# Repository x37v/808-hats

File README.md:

# 808 hihat clone

Based on
[schematic](http://www.ericarcher.net/wp-content/uploads/2014/07/tr-808-hihat-diy-project-revised-dec-2009.pdf)
drawn by [Eric Archer](http://www.ericarcher.net/), which is in turn cloned from the TR-808 Hi Hat.

Drawn in [KiCad 5](http://kicad.org/).

## Mods

* MOTM Power connector
* Trigger conditioning
* Ext audio in
* Noise out
* OH/CH Filtering

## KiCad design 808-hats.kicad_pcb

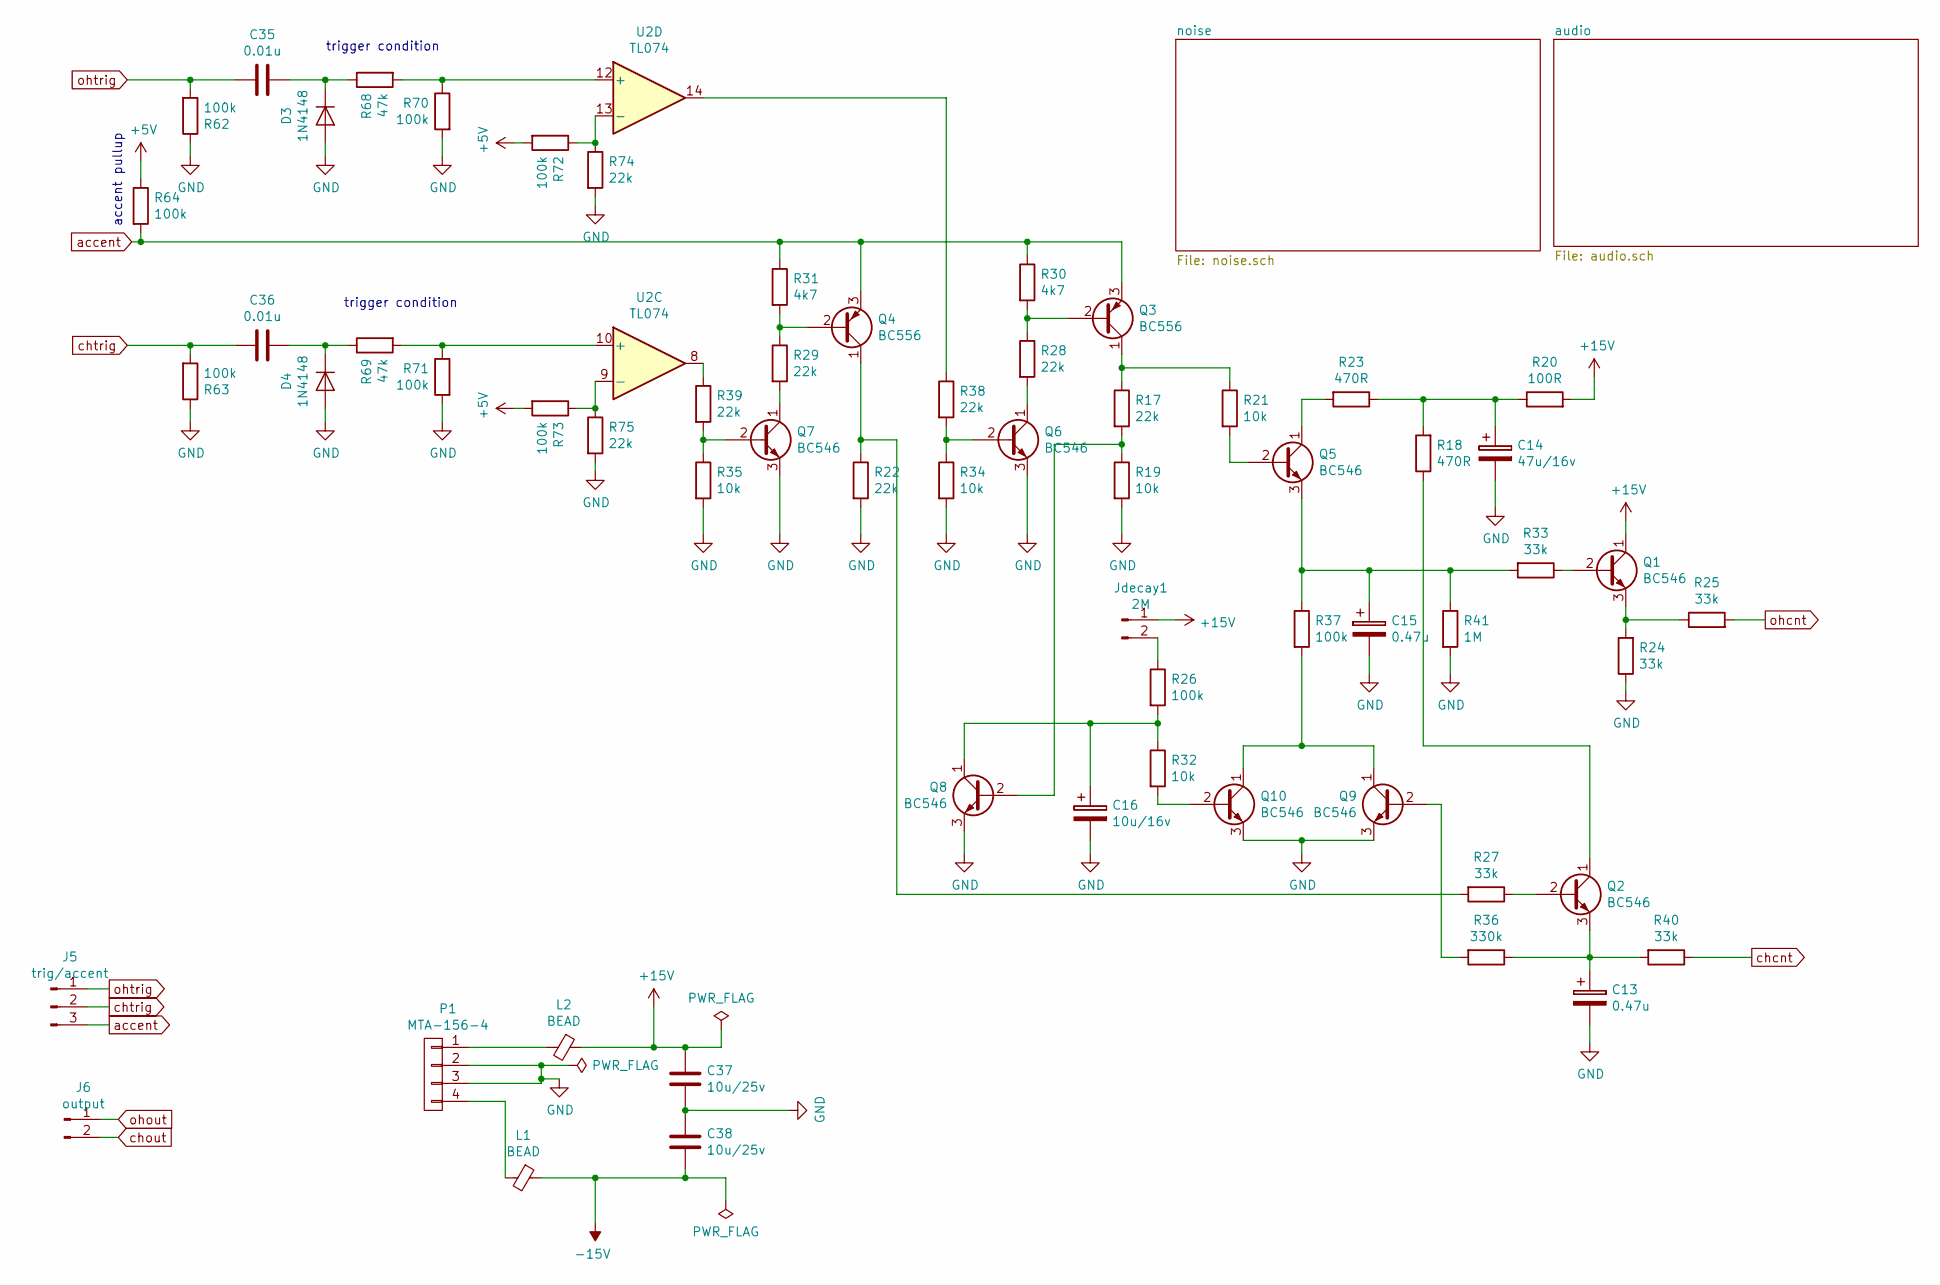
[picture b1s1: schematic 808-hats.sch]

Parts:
C13, C15: 0.47u; CP_Radial_D7.5mm_P2.50mm
C14: 47u/16v; CP_Radial_D7.5mm_P2.50mm
C16: 10u/16v; CP_Radial_D7.5mm_P2.50mm
C35, C36: 0.01u; C_Rect_L7.2mm_W3.0mm_P5.00mm_FKS2_FKP2_MKS2_MKP2
C37, C38: 10u/25v; C_0805_2012Metric_Pad1.33x1.40mm_HandSolder
D3, D4: 1N4148; D_DO-35_SOD27_P7.62mm_Horizontal
J5: trig/accent; PinHeader_1x03_P2.54mm_Vertical
J6: output; PinHeader_1x02_P2.54mm_Vertical
Jdecay1: 2M; PinHeader_1x02_P2.54mm_Vertical
L1, L2: BEAD; R_Axial_DIN0207_L6.3mm_D2.5mm_P10.16mm_Horizontal
P1: MTA-156-4
Q1, Q2, Q5, Q6, Q7, Q8, Q9, Q10: BC546; TO-92L_Inline
Q3, Q4: BC556; TO-92L_Inline
R17, R22, R28, R29, R38, R39, R74, R75: 22k; R_Axial_DIN0204_L3.6mm_D1.6mm_P7.62mm_Horizontal
R18, R23: 470R; R_Axial_DIN0204_L3.6mm_D1.6mm_P7.62mm_Horizontal
R19, R21, R32, R34, R35: 10k; R_Axial_DIN0204_L3.6mm_D1.6mm_P7.62mm_Horizontal
R20: 100R; R_Axial_DIN0204_L3.6mm_D1.6mm_P7.62mm_Horizontal
R24, R25, R27, R33, R40: 33k; R_Axial_DIN0204_L3.6mm_D1.6mm_P7.62mm_Horizontal
R26, R37, R62, R63, R64, R70, R71, R72, R73: 100k; R_Axial_DIN0204_L3.6mm_D1.6mm_P7.62mm_Horizontal
R30, R31: 4k7; R_Axial_DIN0204_L3.6mm_D1.6mm_P7.62mm_Horizontal
R36: 330k; R_Axial_DIN0204_L3.6mm_D1.6mm_P7.62mm_Horizontal
R41: 1M; R_Axial_DIN0204_L3.6mm_D1.6mm_P7.62mm_Horizontal
R68, R69: 47k; R_Axial_DIN0204_L3.6mm_D1.6mm_P7.62mm_Horizontal
U2: TL074; DIP-14_W7.62mm_LongPads

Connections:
+5V: R64.1, R72.2, R73.2; also elsewhere on the board
+15V: C37.1, Jdecay1.1, L2.1, Q1.1 (C), R20.2; also elsewhere on the board
-15V: C38.2, L1.1; also elsewhere on the board
GND: C13.2, C14.2, C15.2, C16.2, C37.2, C38.1, D3.2 (A), D4.2 (A), P1.2, P1.3, Q6.3 (E), Q7.3 (E), Q8.3 (E), Q9.3 (E), Q10.3 (E), R19.2, R22.2, R24.1, R34.2, R35.2, R41.2, R62.1, R63.1, R70.2, R71.2, R74.2, R75.2; also elsewhere on the board
unnamed: C13.1, Q2.3 (E), R36.1, R40.2
unnamed: C14.1, R18.2, R20.1, R23.1
unnamed: C15.1, Q5.3 (E), R33.2, R37.1, R41.1
unnamed: C16.1, Q8.1 (C), R26.2, R32.1
unnamed: C35.1, D3.1 (K), R68.1
unnamed: C36.1, D4.1 (K), R69.1
unnamed: Jdecay1.2, R26.1
unnamed: L1.2, P1.4
unnamed: L2.2, P1.1
unnamed: Q1.2 (B), R33.1
unnamed: Q1.3 (E), R24.2, R25.1
unnamed: Q2.1 (C), R18.1
unnamed: Q2.2 (B), R27.1
unnamed: Q3.1 (C), R17.1, R21.1
unnamed: Q3.2 (B), R28.1, R30.2
unnamed: Q4.1 (C), R22.1, R27.2
unnamed: Q4.2 (B), R29.1, R31.2
unnamed: Q5.1 (C), R23.2
unnamed: Q5.2 (B), R21.2
unnamed: Q6.1 (C), R28.2
unnamed: Q6.2 (B), R34.1, R38.2
unnamed: Q7.1 (C), R29.2
unnamed: Q7.2 (B), R35.1, R39.2
unnamed: Q8.2 (B), R17.2, R19.1
unnamed: Q9.2 (B), R36.2
unnamed: Q9.1 (C), Q10.1 (C), R37.2
unnamed: Q10.2 (B), R32.2
unnamed: R38.1, U2.14
unnamed: R39.1, U2.8
unnamed: R68.2, R70.1, U2.12 (+)
unnamed: R69.2, R71.1, U2.10 (+)
unnamed: R72.1, R74.1, U2.13 (-)
unnamed: R73.1, R75.1, U2.9 (-)
accent: J5.3, Q3.3 (E), Q4.3 (E), R30.1, R31.1, R64.2
chcnt: R40.1; also elsewhere on the board
chout: J6.2; also elsewhere on the board
chtrig: C36.2, J5.2, R63.2
ohcnt: R25.2; also elsewhere on the board
ohout: J6.1; also elsewhere on the board
ohtrig: C35.2, J5.1, R62.2

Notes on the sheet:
trigger condition
accent pullup

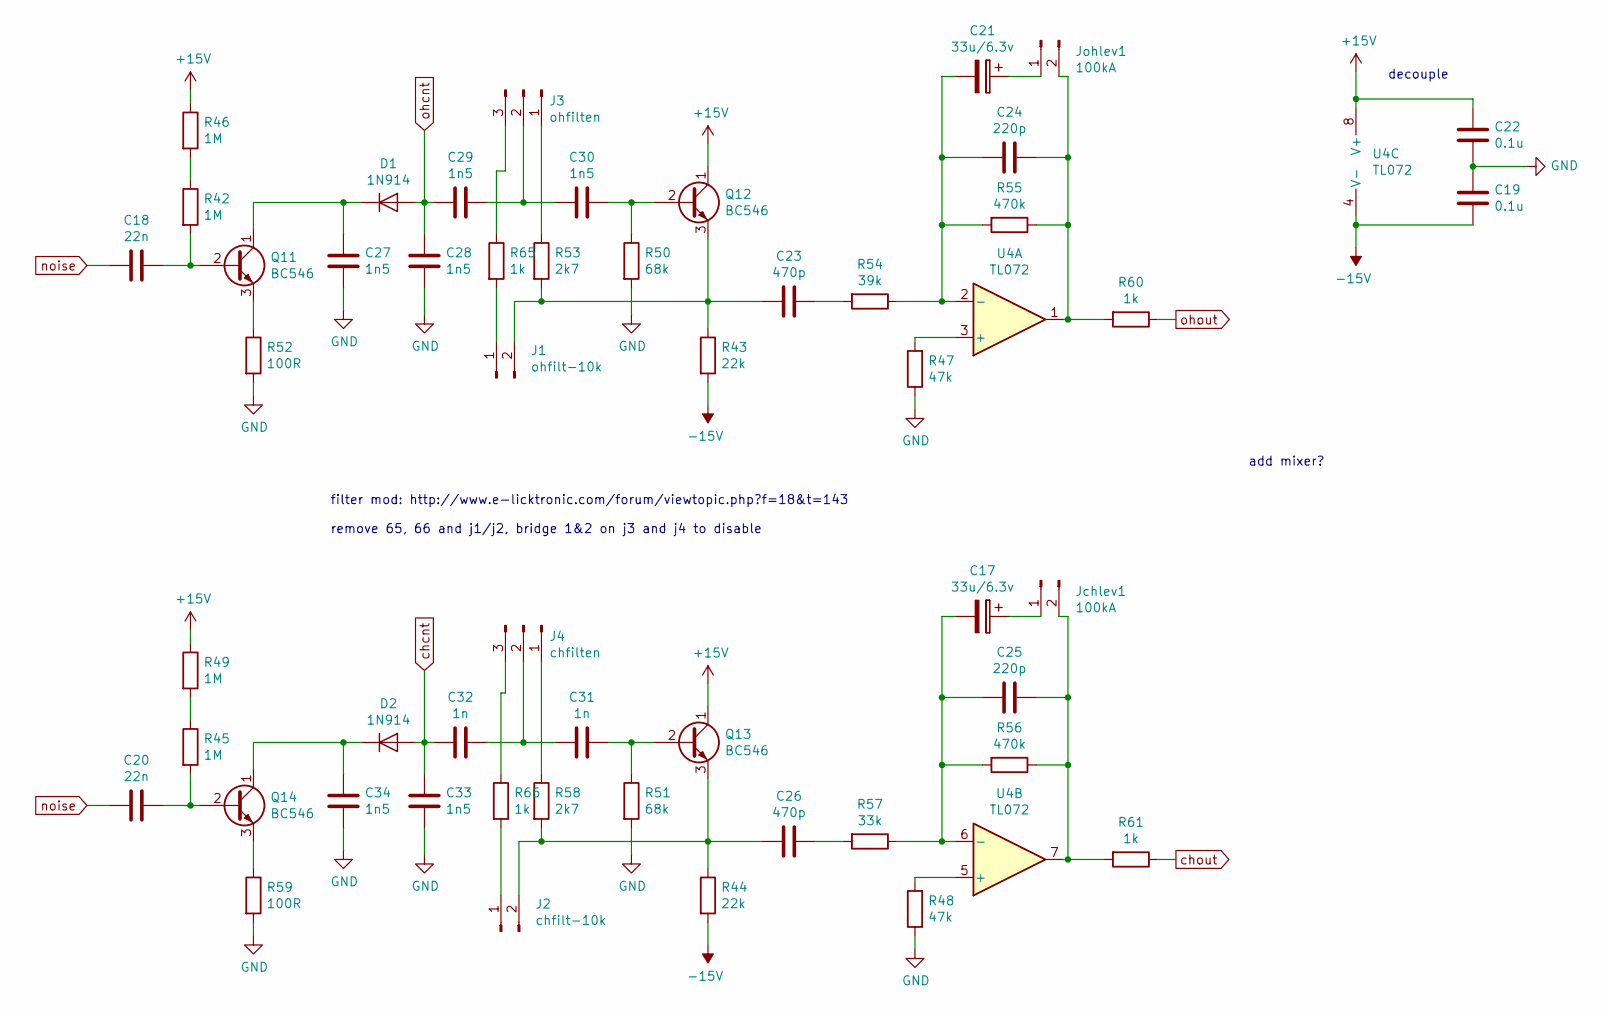
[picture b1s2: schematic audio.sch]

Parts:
C17, C21: 33u/6.3v; CP_Radial_D7.5mm_P2.50mm
C18, C20: 22n; C_Disc_D4.3mm_W1.9mm_P5.00mm
C19, C22: 0.1u; C_Disc_D3.4mm_W2.1mm_P2.50mm
C23, C26: 470p; C_Disc_D4.3mm_W1.9mm_P5.00mm
C24, C25: 220p; C_Disc_D4.3mm_W1.9mm_P5.00mm
C27, C28, C29, C30, C33, C34: 1n5; C_Disc_D3.4mm_W2.1mm_P2.50mm
C31, C32: 1n; C_Disc_D3.4mm_W2.1mm_P2.50mm
D1, D2: 1N914; D_DO-35_SOD27_P7.62mm_Horizontal
J1: ohfilt-10k; PinHeader_1x02_P2.54mm_Vertical
J2: chfilt-10k; PinHeader_1x02_P2.54mm_Vertical
J3: ohfilten; PinHeader_1x03_P2.54mm_Vertical
J4: chfilten; PinHeader_1x03_P2.54mm_Vertical
Jchlev1: 100kA; PinHeader_1x02_P2.54mm_Vertical
Johlev1: 100kA; PinHeader_1x02_P2.54mm_Vertical
Q11, Q12, Q13, Q14: BC546; TO-92L_Inline
R42, R45, R46, R49: 1M; R_Axial_DIN0204_L3.6mm_D1.6mm_P7.62mm_Horizontal
R43, R44: 22k; R_Axial_DIN0204_L3.6mm_D1.6mm_P7.62mm_Horizontal
R47, R48: 47k; R_Axial_DIN0204_L3.6mm_D1.6mm_P7.62mm_Horizontal
R50, R51: 68k; R_Axial_DIN0204_L3.6mm_D1.6mm_P7.62mm_Horizontal
R52, R59: 100R; R_Axial_DIN0204_L3.6mm_D1.6mm_P7.62mm_Horizontal
R53, R58: 2k7; R_Axial_DIN0204_L3.6mm_D1.6mm_P7.62mm_Horizontal
R54: 39k; R_Axial_DIN0204_L3.6mm_D1.6mm_P7.62mm_Horizontal
R55, R56: 470k; R_Axial_DIN0204_L3.6mm_D1.6mm_P7.62mm_Horizontal
R57: 33k; R_Axial_DIN0204_L3.6mm_D1.6mm_P7.62mm_Horizontal
R60, R61, R65, R66: 1k; R_Axial_DIN0204_L3.6mm_D1.6mm_P7.62mm_Horizontal
U4: TL072; DIP-8_W7.62mm_LongPads

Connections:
+15V: C22.1, Q12.1 (C), Q13.1 (C), R46.1, R49.1, U4.8 (V+); also elsewhere on the board
-15V: C19.2, R43.2, R44.2, U4.4 (V-); also elsewhere on the board
GND: C19.1, C22.2, C27.1, C28.1, C33.1, C34.1, R47.1, R48.1, R50.2, R51.2, R52.2, R59.2; also elsewhere on the board
unnamed: C17.1, Jchlev1.1
unnamed: C17.2, C25.2, R56.2, R57.1, U4.6 (-)
unnamed: C18.1, Q11.2 (B), R42.2
unnamed: C20.1, Q14.2 (B), R45.2
unnamed: C21.1, Johlev1.1
unnamed: C21.2, C24.2, R54.1, R55.2, U4.2 (-)
unnamed: C23.1, J1.2, Q12.3 (E), R43.1, R53.2
unnamed: C23.2, R54.2
unnamed: C24.1, Johlev1.2, R55.1, R60.2, U4.1
unnamed: C25.1, Jchlev1.2, R56.1, R61.2, U4.7
unnamed: C26.1, J2.2, Q13.3 (E), R44.1, R58.2
unnamed: C26.2, R57.2
unnamed: C27.2, D1.1 (K), Q11.1 (C)
unnamed: C29.2, C30.1, J3.2
unnamed: C30.2, Q12.2 (B), R50.1
unnamed: C31.1, C32.2, J4.2
unnamed: C31.2, Q13.2 (B), R51.1
unnamed: C34.2, D2.1 (K), Q14.1 (C)
unnamed: J1.1, R65.2
unnamed: J2.1, R66.2
unnamed: J3.1, R53.1
unnamed: J3.3, R65.1
unnamed: J4.1, R58.1
unnamed: J4.3, R66.1
unnamed: Q11.3 (E), R52.1
unnamed: Q14.3 (E), R59.1
unnamed: R42.1, R46.2
unnamed: R45.1, R49.2
unnamed: R47.2, U4.3 (+)
unnamed: R48.2, U4.5 (+)
chcnt: C32.1, C33.2, D2.2 (A); also elsewhere on the board
chout: R61.1; also elsewhere on the board
noise: C18.2, C20.2; also elsewhere on the board
ohcnt: C28.2, C29.1, D1.2 (A); also elsewhere on the board
ohout: R60.1; also elsewhere on the board

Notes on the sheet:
add mixer?
decouple
filter mod: http://www.e-licktronic.com/forum/viewtopic.php?f=18&t=143 remove 65, 66 and j1/j2, bridge 1&2 on j3 and j4 to disable

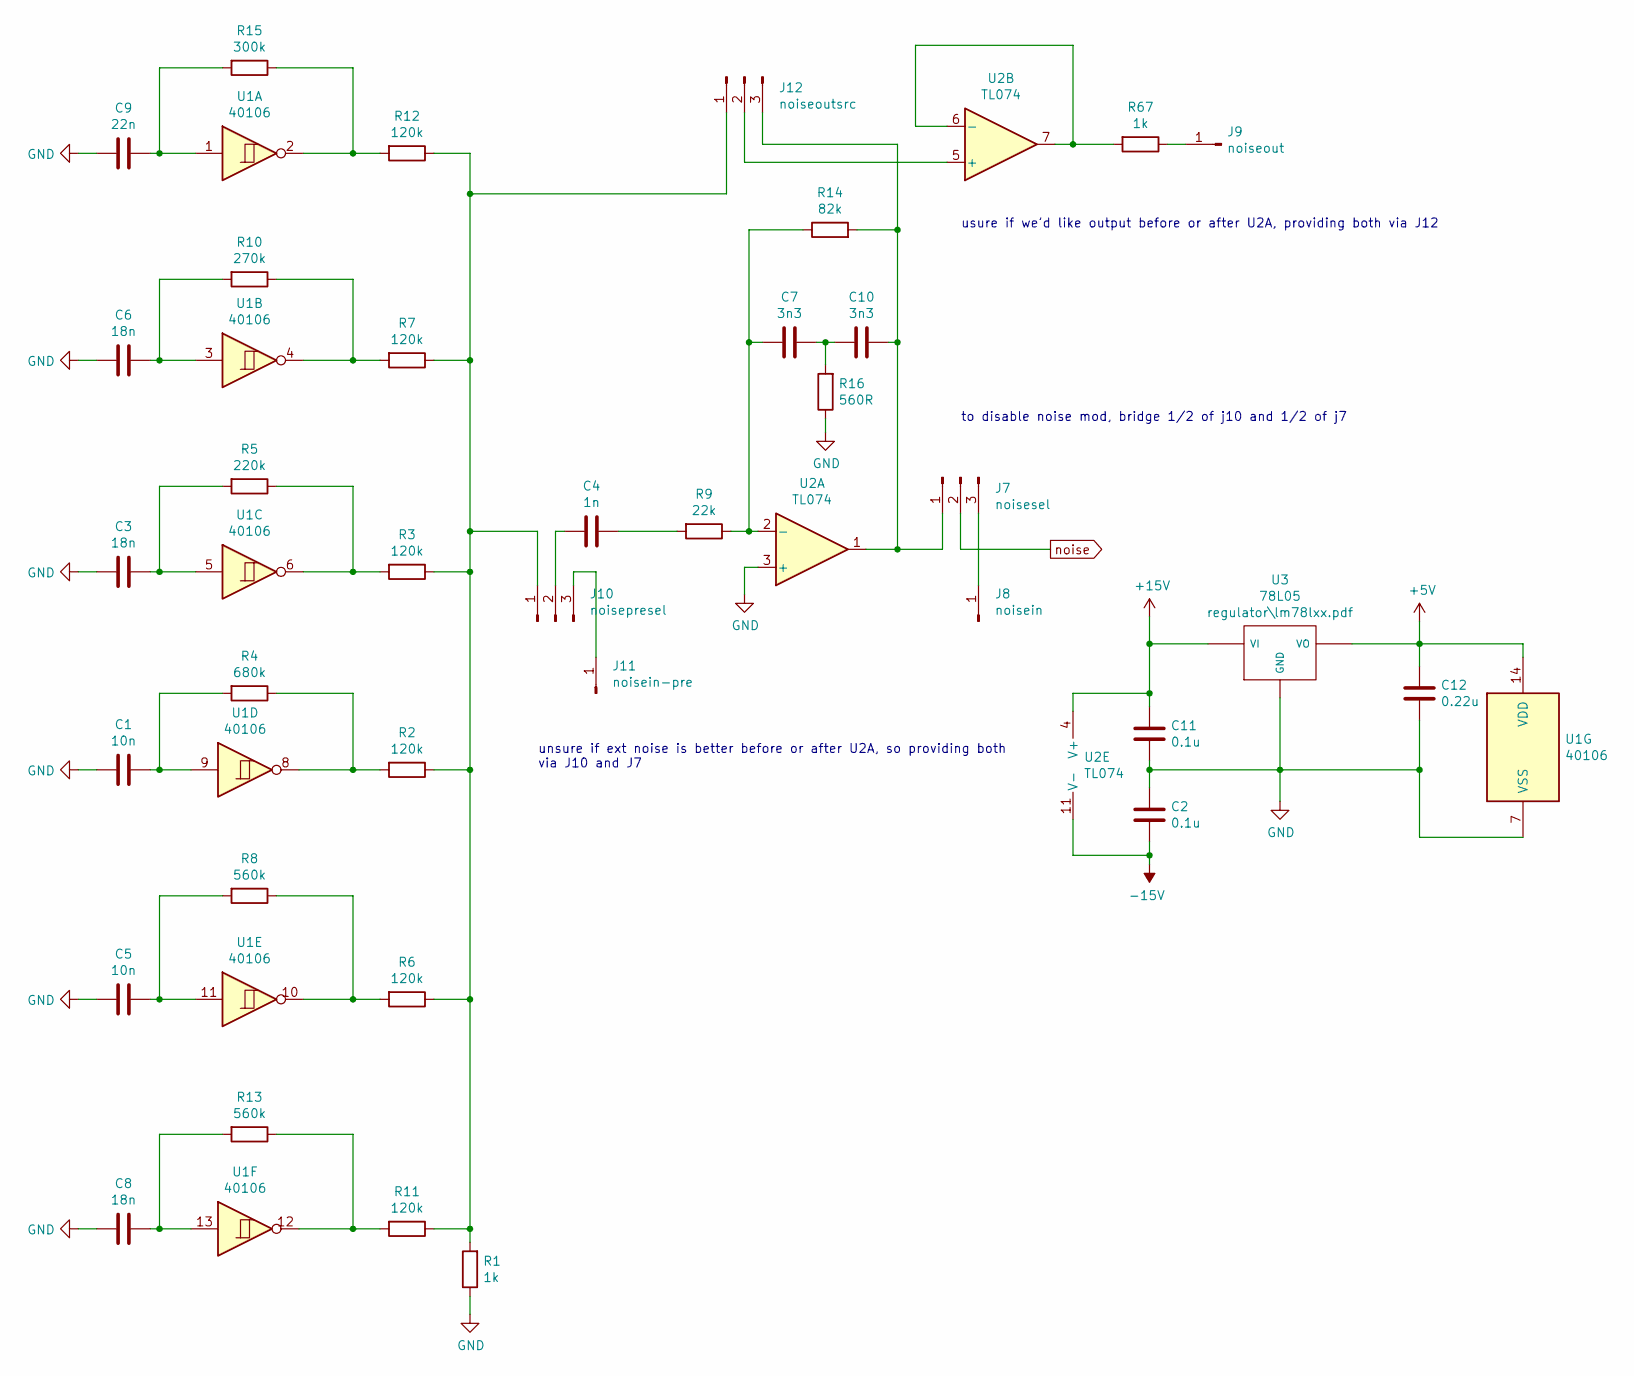
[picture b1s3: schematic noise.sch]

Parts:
C1, C5: 10n; C_Disc_D3.4mm_W2.1mm_P2.50mm
C2, C11: 0.1u; C_Disc_D3.4mm_W2.1mm_P2.50mm
C3, C6, C8: 18n; C_Disc_D3.4mm_W2.1mm_P2.50mm
C4: 1n; C_Disc_D3.4mm_W2.1mm_P2.50mm
C7, C10: 3n3; C_Disc_D3.4mm_W2.1mm_P2.50mm
C9: 22n; C_Disc_D4.3mm_W1.9mm_P5.00mm
C12: 0.22u; C_Disc_D3.4mm_W2.1mm_P2.50mm
J7: noisesel; PinHeader_1x03_P2.54mm_Vertical
J8: noisein; PinHeader_1x01_P2.54mm_Vertical
J9: noiseout; PinHeader_1x01_P2.54mm_Vertical
J10: noisepresel; PinHeader_1x03_P2.54mm_Vertical
J11: noisein-pre; PinHeader_1x01_P2.54mm_Vertical
J12: noiseoutsrc; PinHeader_1x03_P2.54mm_Vertical
R1, R67: 1k; R_Axial_DIN0204_L3.6mm_D1.6mm_P7.62mm_Horizontal
R2, R3, R6, R7, R11, R12: 120k; R_Axial_DIN0204_L3.6mm_D1.6mm_P7.62mm_Horizontal
R4: 680k; R_Axial_DIN0204_L3.6mm_D1.6mm_P7.62mm_Horizontal
R5: 220k; R_Axial_DIN0204_L3.6mm_D1.6mm_P7.62mm_Horizontal
R8, R13: 560k; R_Axial_DIN0204_L3.6mm_D1.6mm_P7.62mm_Horizontal
R9: 22k; R_Axial_DIN0204_L3.6mm_D1.6mm_P7.62mm_Horizontal
R10: 270k; R_Axial_DIN0204_L3.6mm_D1.6mm_P7.62mm_Horizontal
R14: 82k; R_Axial_DIN0204_L3.6mm_D1.6mm_P7.62mm_Horizontal
R15: 300k; R_Axial_DIN0204_L3.6mm_D1.6mm_P7.62mm_Horizontal
R16: 560R; R_Axial_DIN0204_L3.6mm_D1.6mm_P7.62mm_Horizontal
U1: 40106; DIP-14_W7.62mm_LongPads
U2: TL074; DIP-14_W7.62mm_LongPads
U3: 78L05; TO-220-3_Vertical

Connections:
+5V: C12.1, U1.14 (VDD), U3.3 (VO); also elsewhere on the board
+15V: C11.1, U2.4 (V+), U3.1 (VI); also elsewhere on the board
-15V: C2.2, U2.11 (V-); also elsewhere on the board
GND: C1.2, C2.1, C3.2, C5.2, C6.2, C8.2, C9.2, C11.2, C12.2, R1.1, R16.1, U1.7 (VSS), U2.3 (+), U3.2 (GND); also elsewhere on the board
unnamed: C1.1, R4.2, U1.9
unnamed: C3.1, R5.2, U1.5
unnamed: C4.1, R9.2
unnamed: C4.2, J10.2
unnamed: C5.1, R8.2, U1.11
unnamed: C6.1, R10.2, U1.3
unnamed: C7.2, R9.1, R14.1, U2.2 (-)
unnamed: C8.1, R13.2, U1.13
unnamed: C9.1, R15.2, U1.1
unnamed: C10.1, J7.1, J12.3, R14.2, U2.1
unnamed: C7.1, C10.2, R16.2
unnamed: J7.3, J8.1
unnamed: J9.1, R67.1
unnamed: J10.1, J12.1, R1.2, R2.1, R3.1, R6.1, R7.1, R11.1, R12.1
unnamed: J10.3, J11.1
unnamed: J12.2, U2.5 (+)
unnamed: R2.2, R4.1, U1.8
unnamed: R3.2, R5.1, U1.6
unnamed: R6.2, R8.1, U1.10
unnamed: R7.2, R10.1, U1.4
unnamed: R11.2, R13.1, U1.12
unnamed: R12.2, R15.1, U1.2
unnamed: R67.2, U2.6 (-), U2.7
noise: J7.2; also elsewhere on the board

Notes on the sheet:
unsure if ext noise is better before or after U2A, so providing both via J10 and J7
usure if we'd like output before or after U2A, providing both via J12
to disable noise mod, bridge 1/2 of j10 and 1/2 of j7

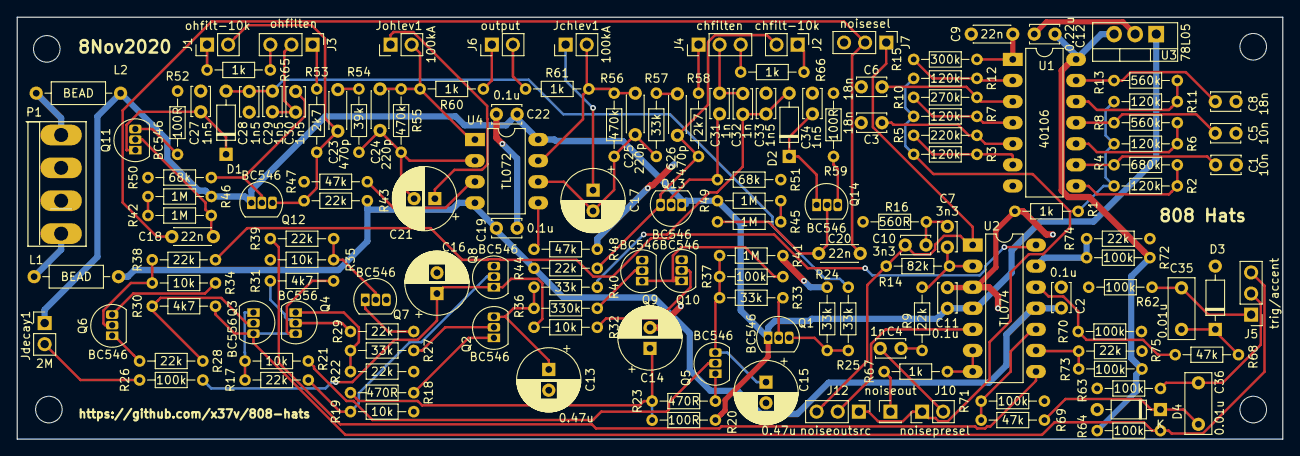
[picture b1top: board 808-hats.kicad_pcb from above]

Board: 2 copper layers, 152.4 x 50.8 mm, 149 parts (0 on the bottom side), 96 nets.

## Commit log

2019-04-13 initial commit
    need to add trigger conditioning
2019-04-13 added trigger conditioning and accent pullup
2019-04-13 added power
2019-04-14 fixup noise generator connections
2019-04-14 added filter mod
2019-04-14 noise in/out with selection
2019-04-14 noise mods
2019-04-14 readme
2019-04-14 indicate kicad
2019-04-14 power
2019-04-14 removed labels
2019-04-27 added hex-inverter style trigger conditioning (amplification?)
    https://static1.squarespace.com/static/54c8f37ae4b015761b133d43/550b9d69e4b0c859c95703b9/550b9d69e4b0c859c95703ba/1426824558402/NeinOhNein_KICK_v1_schem.png?format=2500w
2019-04-27 cleanup
2019-05-03 selected some parts
2019-05-04 assigned footprints
2019-05-05 oops, through hole for bead
2019-05-05 starting layout
2019-05-06 a lot more layout
2019-05-07 more layout
2019-05-07 squishing
2020-11-08 much layout work
2020-11-08 exposed and moved around value labels
2020-11-08 setup design rules
2020-11-09 fully routed, removed some i/o that could move onto switches
2020-11-09 labels, .. final layout?
2021-11-10 Update README.md
    https://forum.kicad.info/t/warning-avoid-all-links-to-kicad-pcb-org-use-kicad-org/31521
